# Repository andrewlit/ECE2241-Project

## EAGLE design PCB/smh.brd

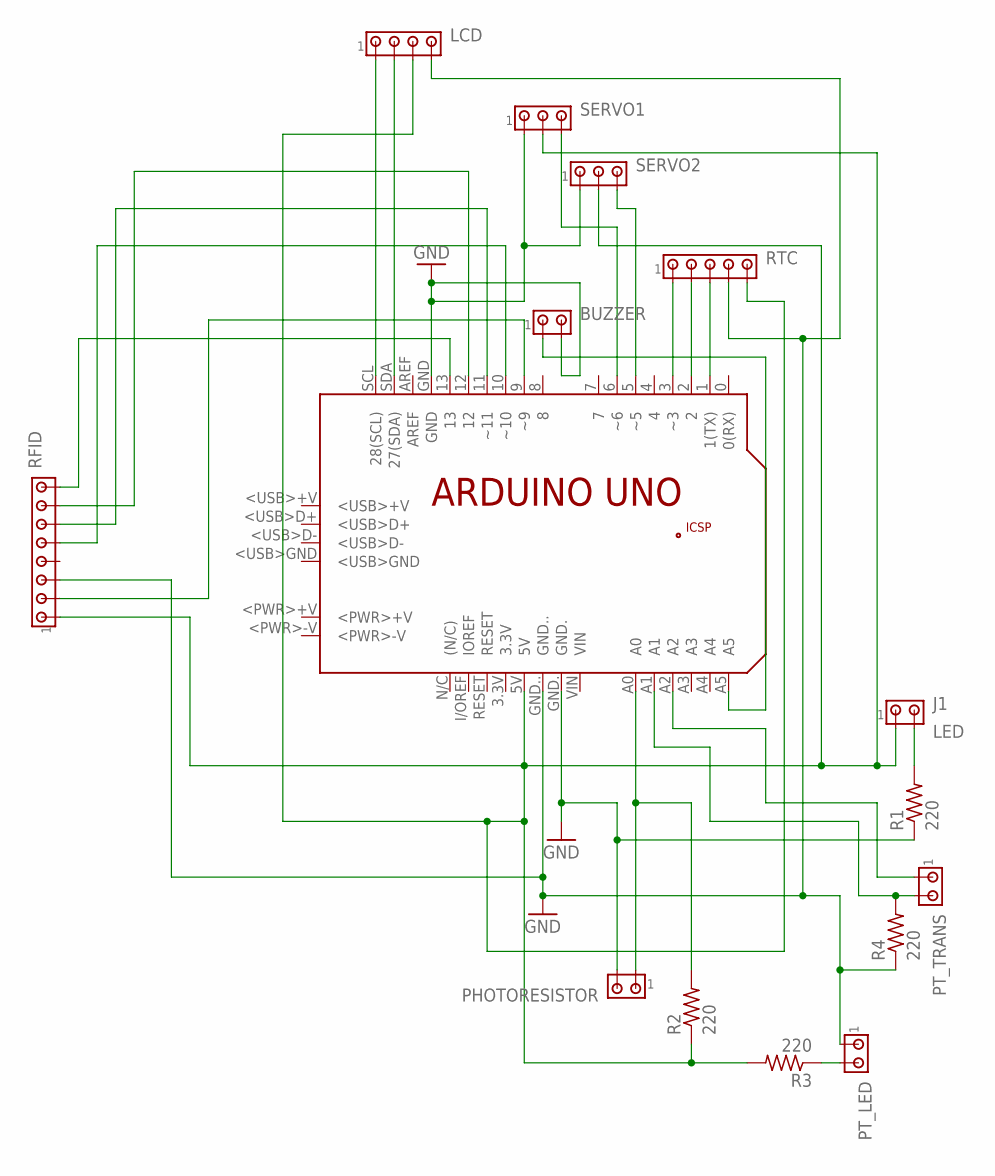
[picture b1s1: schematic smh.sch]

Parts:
BUZZER: MTA02-100; 10X02MTA
J1: LED; 10X02MTA
LCD: MTA04-100; 10X04MTA
PCB1: ARDUINO_UNO
PHOTORESISTOR: MTA02-100; 10X02MTA
PT_LED: MTA02-100; 10X02MTA
PT_TRANS: MTA02-100; 10X02MTA
R1, R2, R3, R4: 220; 0309/10
RFID: MTA08-100; 10X08MTA
RTC: MTA05-100; 10X05MTA
SERVO1, SERVO2: MTA03-100; 10X03MTA

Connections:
GND: BUZZER.2, LCD.4, PCB1.GND, PCB1.GND., PCB1.GND.., PHOTORESISTOR.2, PT_LED.1, R1.1, R4.1, RFID.3, RTC.4, SERVO1.1, SERVO2.1
unnamed: BUZZER.1, PCB1.A5
unnamed: LCD.2, PCB1.SDA (27(SDA))
unnamed: PCB1.1 (1(TX)), RTC.3
unnamed: PCB1.2, RTC.2
unnamed: PCB1.6 (~6), SERVO1.3
unnamed: PCB1.3 (~3), RTC.1
unnamed: PCB1.5 (~5), SERVO2.3
unnamed: LCD.1, PCB1.SCL (28(SCL))
unnamed: PT_LED.2, R3.1
unnamed: PCB1.A0, PHOTORESISTOR.1, R2.2
unnamed: J1.1, LCD.3, PCB1.5V, R2.1, R3.2, RFID.1, RTC.5, SERVO1.2, SERVO2.2
unnamed: PCB1.9 (~9), RFID.2
unnamed: J1.2, R1.2
unnamed: PCB1.13, RFID.8
unnamed: PCB1.10 (~10), RFID.5
unnamed: PCB1.11 (~11), RFID.6
unnamed: PCB1.12, RFID.7
unnamed: PCB1.A1, PT_TRANS.2, R4.2
unnamed: PCB1.A2, PT_TRANS.1

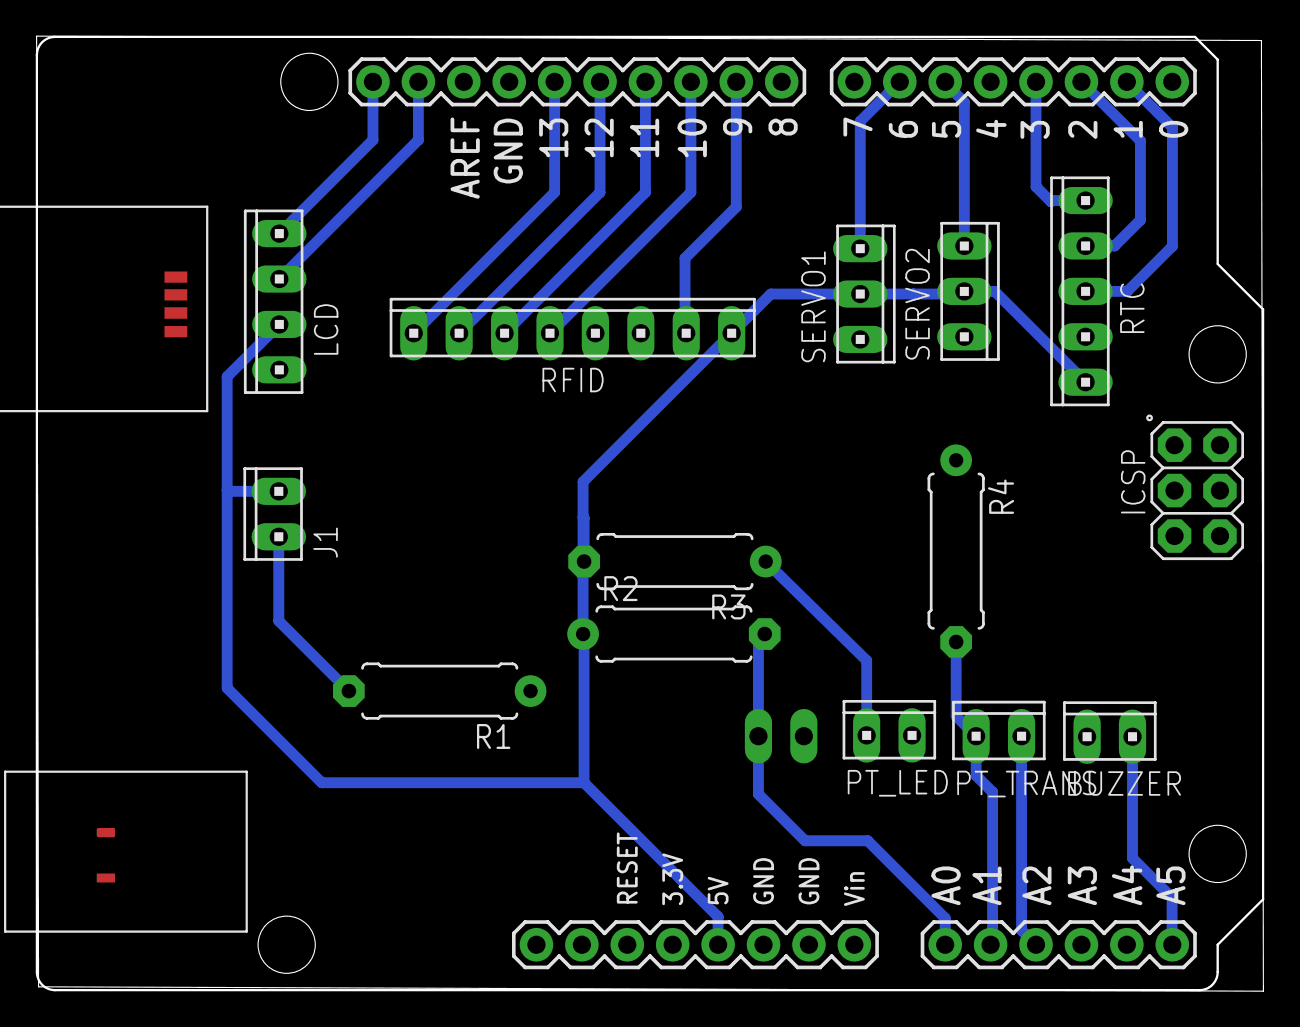
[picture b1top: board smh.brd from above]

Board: 2 copper layers, 68.6 x 53.3 mm, 15 parts (1 on the bottom side), 20 nets.

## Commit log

2018-03-10 Initial commit to the project repo
2018-03-13 Added gitignore
2018-03-13 Refactored and added the PCB to project repo
2018-03-16 Implemented intializations
    The dispense() function is also being worked on, but is incomplete.
    That is the current point of development
2018-03-16 Dispense drafted
    There are probably some features missing, but the majority of the code
    for the dispense function has at least been drafted in. Ther are some
    constants that need to be updated for the actual device, and line 191
    needs to be updated to properly show an error message.
    The dispense function also needs to have the "success" portion of the
    code added, as the current function only deals with error checking,
2018-03-22 Added Dispensing
    Dispensing is now more complete. A success function has been added.
    Revision should be done to ensure proper operation. Display still needs
    to be worked on, as does the RTC and general UI.
    Completion of the dispense function will likely require at least a
    partially complete prototype. Efforts will now focus more on the UI and
    RTC implemnetation, until hardware is in place to help test the
2018-03-22 rfid
2018-03-22 added to rfid
2018-03-22 Update rfid
